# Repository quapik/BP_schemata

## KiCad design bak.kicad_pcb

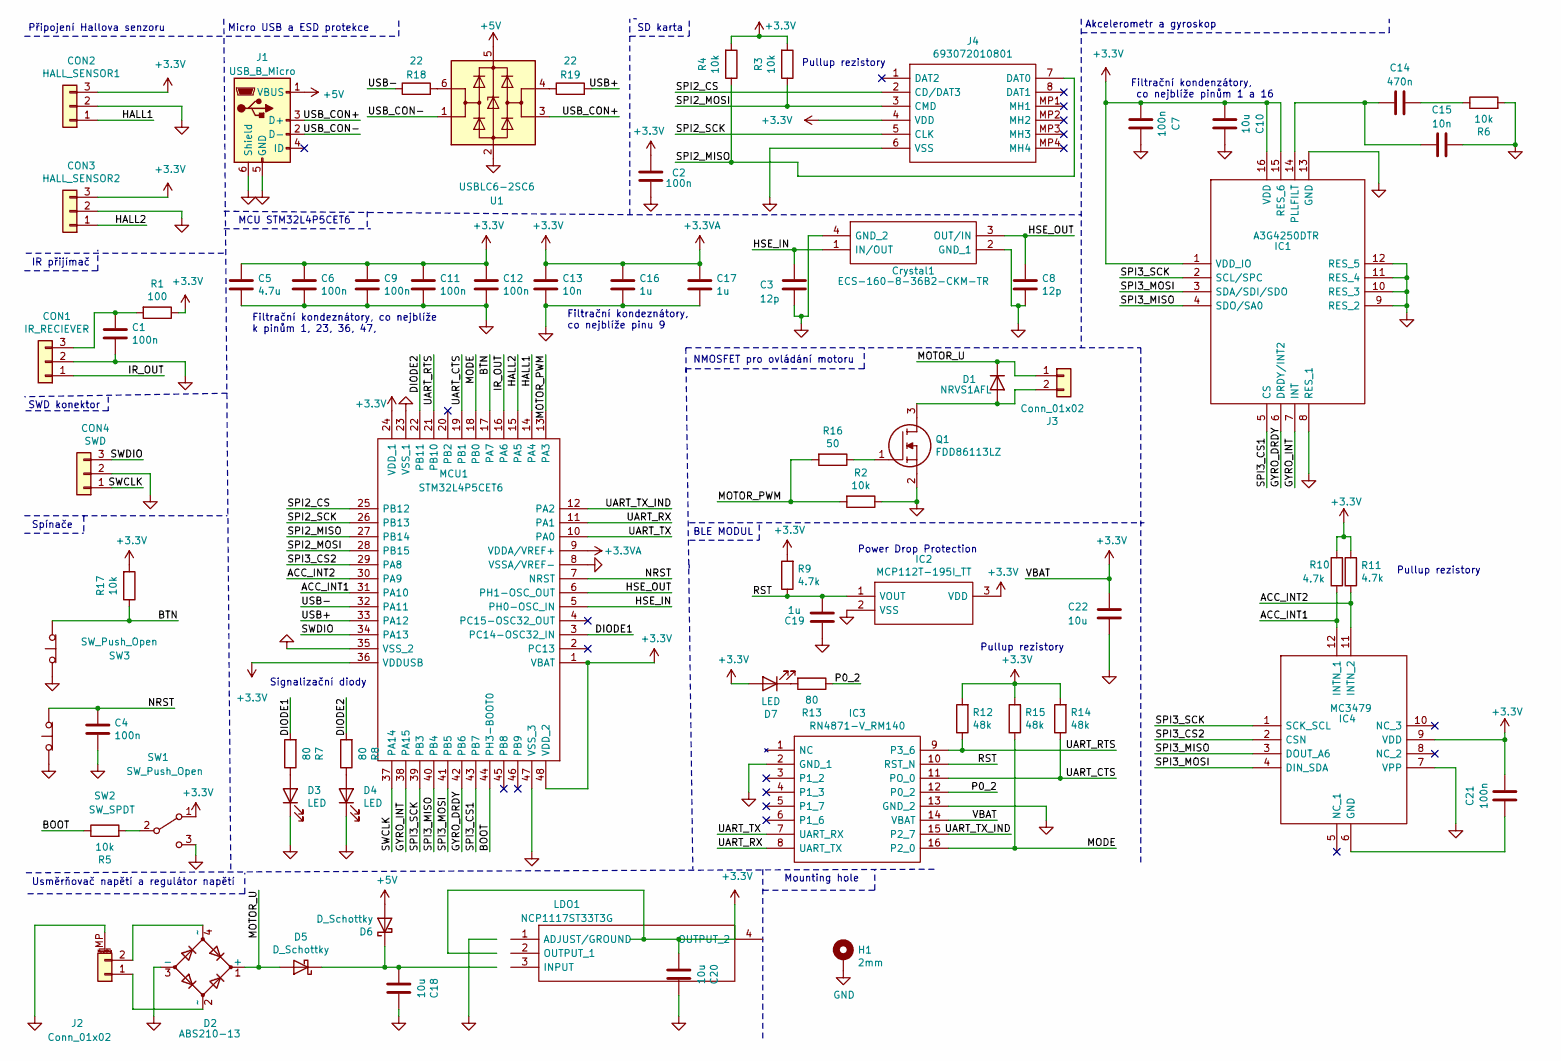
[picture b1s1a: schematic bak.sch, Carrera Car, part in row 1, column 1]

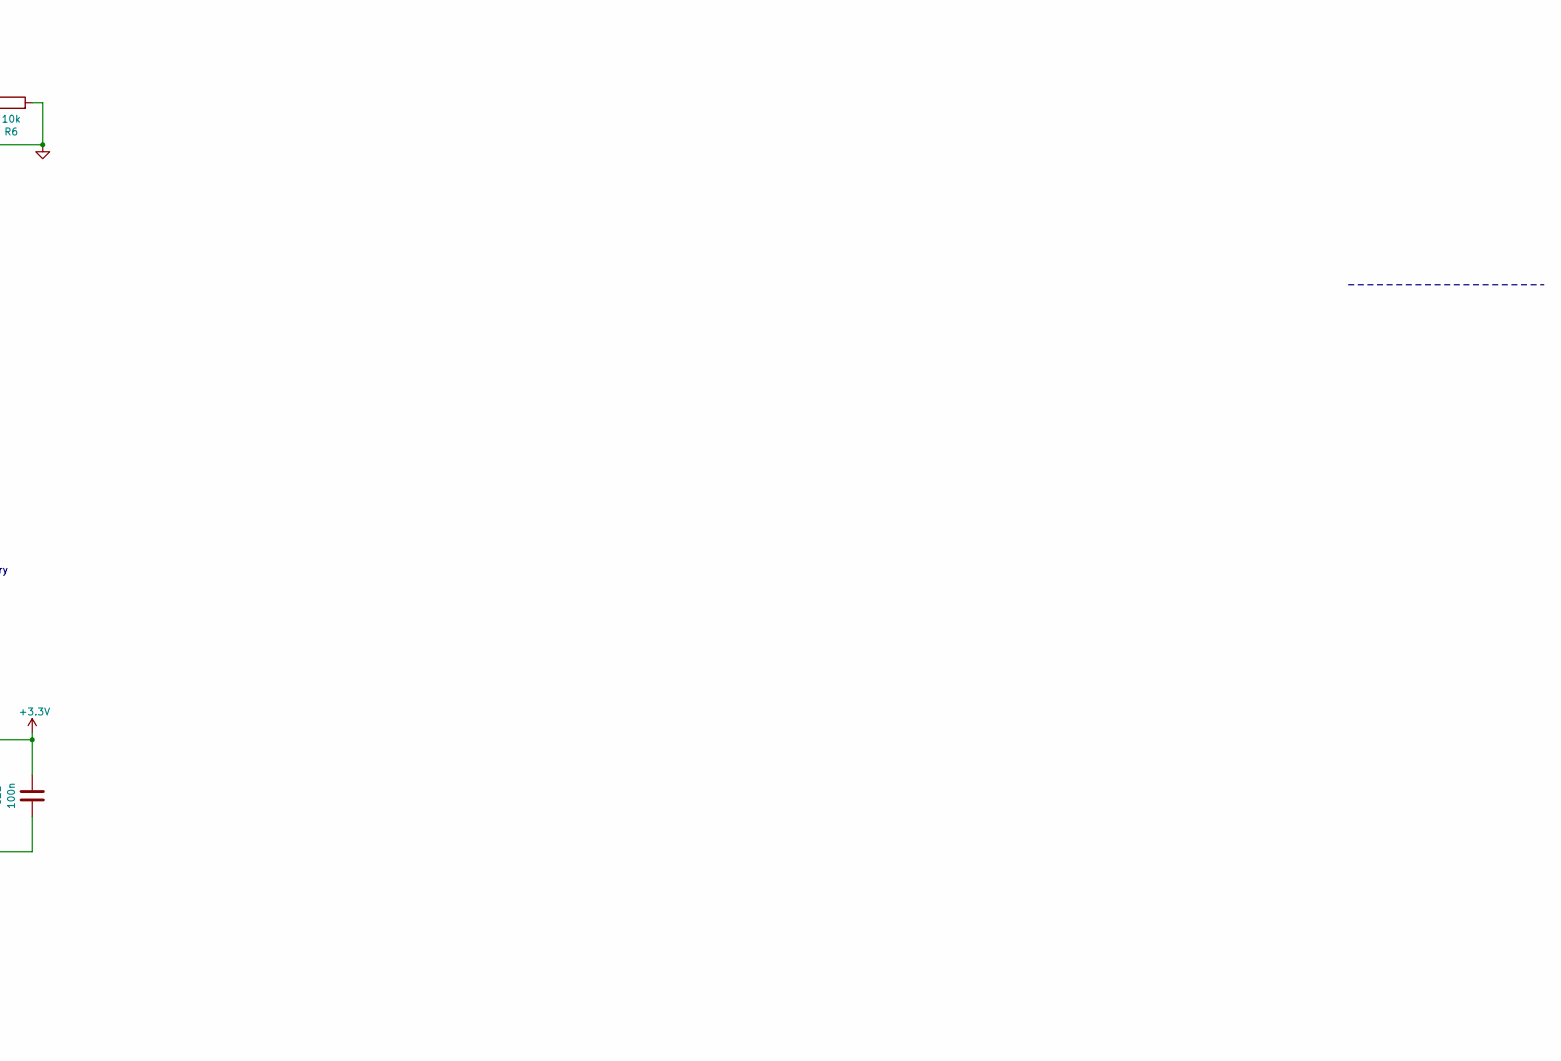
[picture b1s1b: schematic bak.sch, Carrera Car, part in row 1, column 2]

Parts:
C1, C2, C4, C6, C7, C9, C11, C12, C21: 100n; C_0805_2012Metric_Pad1.18x1.45mm_HandSolder
C3, C8: 12p; C_0603_1608Metric_Pad1.08x0.95mm_HandSolder
C5: 4.7u; C_0603_1608Metric_Pad1.08x0.95mm_HandSolder
C10, C22: 10u; C_0805_2012Metric_Pad1.18x1.45mm_HandSolder
C13, C15: 10n; C_0603_1608Metric_Pad1.08x0.95mm_HandSolder
C14: 470n; C_0603_1608Metric_Pad1.08x0.95mm_HandSolder
C16, C17, C19: 1u; C_0603_1608Metric_Pad1.08x0.95mm_HandSolder
C18, C20: 10u; C_1210_3225Metric_Pad1.33x2.70mm_HandSolder
CON1: IR_RECIEVER; MyConnector3
CON2: HALL_SENSOR1; MyConnector3
CON3: HALL_SENSOR2; MyConnector3
CON4: SWD; MyConnector3
Crystal1: ECS-160-8-36B2-CKM-TR; ECS160836B2CKMTR; Mouser Part Number 520-160-8-36B2-CKMTR
D1: NRVS1AFL; D_SOD-123F
D2: ABS210-13; ABS21013
D3, D4, D7: LED; D_0805_2012Metric_Pad1.15x1.40mm_HandSolder
D5, D6: D_Schottky; D_SOD-323_HandSoldering
H1: 2mm; MountingHole_2.7mm_M2.5_Pad_Via
IC1: A3G4250DTR; LGA-16L_4X4X1.1MM_; Mouser Part Number 511-A3G4250DTR
IC2: MCP112T-195I_TT; SOT95P237X112-3N; Mouser Part Number 579-MCP112T-195I/TT
IC3: RN4871-V_RM140; RN4871VRM140; Mouser Part Number 579-RN4871-V/RM140
IC4: MC3479; Mouser Part Number 498-MC3479
J1: USB_B_Micro; USB30653000A
J2: Conn_01x02; Conn01x02_my
J3: Conn_01x02; MyConnector2
J4: 693072010801; Mouser Part Number 710-693072010801
LDO1: NCP1117ST33T3G; SOT230P700X180-4N; Mouser Part Number 863-NCP1117ST33T3G
MCU1: STM32L4P5CET6; QFP50P900X900X160-48N; Mouser Part Number 511-STM32L4P5CET6
Q1: FDD86113LZ; DPAK3-CASE-369AS; Mouser Part Number 512-FDD86113LZ
R1: 100; R_0805_2012Metric_Pad1.20x1.40mm_HandSolder
R2, R3, R4, R5, R6, R17: 10k; R_0805_2012Metric_Pad1.20x1.40mm_HandSolder
R7, R8, R13: 80; R_0805_2012Metric_Pad1.20x1.40mm_HandSolder
R9, R10, R11: 4.7k; R_0603_1608Metric_Pad0.98x0.95mm_HandSolder
R12, R14, R15: 48k; R_0603_1608Metric_Pad0.98x0.95mm_HandSolder
R16: 50; R_0805_2012Metric_Pad1.20x1.40mm_HandSolder
R18, R19: 22; R_0603_1608Metric_Pad0.98x0.95mm_HandSolder
SW1, SW3: SW_Push_Open; PTS815SJM250SMTRLFS
SW2: SW_SPDT; SSSS810701
U1: USBLC6-2SC6; SOT-23-6

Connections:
+3.3VA: C2.2, C5.1, C6.1, C7.2, C9.1, C10.2, C11.1, C12.1, C13.1, C16.1, C17.1, C20.2, C21.2, C22.1, CON2.3, CON3.3, D7.2 (A), IC1.1 (VDD_IO), IC1.15 (RES_6), IC1.16 (VDD), IC2.3 (VDD), IC3.14 (VBAT), IC4.9 (VDD), J4.4 (VDD), LDO1.2 (OUTPUT_1), LDO1.4 (OUTPUT_2), MCU1.1 (VBAT), MCU1.9 (VDDA/VREF+), MCU1.24 (VDD_1), MCU1.36 (VDDUSB), MCU1.48 (VDD_2), R1.1, R3.2, R4.2, R9.2, R10.2, R11.2, R12.2, R14.2, R15.2, R17.2, SW2.1 (A)
+5V: D6.2 (A), J1.1 (VBUS), U1.5 (VBUS)
/ACC_INT1: IC4.12 (INTN_1), MCU1.31 (PA10), R10.1
/ACC_INT2: IC4.11 (INTN_2), MCU1.30 (PA9), R11.1
/BOOT: MCU1.44 (PH3-BOOT0), R5.1
/BTN: MCU1.17 (PA7), R17.1, SW3.2 (B)
/DIODE1: MCU1.3 (PC14-OSC32_IN), R7.2
/DIODE2: MCU1.22 (PB11), R8.2
/GYRO_DRDY: IC1.6 (DRDY/INT2), MCU1.42 (PB6)
/GYRO_INT: IC1.7 (INT), MCU1.38 (PA15)
/HALL1: CON2.1, MCU1.14 (PA4)
/HALL2: CON3.1, MCU1.15 (PA5)
/HSE_IN: C3.1, Crystal1.1 (IN/OUT), MCU1.5 (PH0-OSC_IN)
/HSE_OUT: C8.1, Crystal1.3 (OUT/IN), MCU1.6 (PH1-OSC_OUT)
/IR_OUT: CON1.1, MCU1.16 (PA6)
/MODE: IC3.16 (P2_0), MCU1.18 (PB0), R15.1
/MOTOR+: D1.1 (K), D2.1 (+), D5.2 (A), J3.1
/MOTOR-: D1.2 (A), J3.2, Q1.3
/MOTOR_PWM: MCU1.13 (PA3), R2.2, R16.2
/NRST: C4.1, MCU1.7 (NRST), SW1.2 (B)
/P0_2: IC3.12 (P0_2), R13.1
/RST: C19.1, IC2.1 (VOUT), IC3.10 (RST_N), R9.1
/SPI2_CS: J4.2 (CD/DAT3), MCU1.25 (PB12)
/SPI2_MISO: J4.7 (DAT0), MCU1.27 (PB14), R4.1
/SPI2_MOSI: J4.3 (CMD), MCU1.28 (PB15), R3.1
/SPI2_SCK: J4.5 (CLK), MCU1.26 (PB13)
/SPI3_CS1: IC1.5 (CS), MCU1.43 (PB7)
/SPI3_CS2: IC4.2 (CSN), MCU1.29 (PA8)
/SPI3_MISO: IC1.4 (SDO/SA0), IC4.3 (DOUT_A6), MCU1.40 (PB4)
/SPI3_MOSI: IC1.3 (SDA/SDI/SDO), IC4.4 (DIN_SDA), MCU1.41 (PB5)
/SPI3_SCK: IC1.2 (SCL/SPC), IC4.1 (SCK_SCL), MCU1.39 (PB3)
/SWCLK: CON4.1, MCU1.37 (PA14)
/SWDIO: CON4.3, MCU1.34 (PA13)
/UART_CTS: IC3.11 (PO_0), MCU1.19 (PB1), R14.1
/UART_RTS: IC3.9 (P3_6), MCU1.21 (PB10), R12.1
/UART_RX: IC3.8 (UART_TX), MCU1.11 (PA1)
/UART_TX: IC3.7 (UART_RX), MCU1.10 (PA0)
/UART_TX_IND: IC3.15 (P2_7), MCU1.12 (PA2)
/USB+: MCU1.33 (PA12), R19.2
/USB-: MCU1.32 (PA11), R18.1
/USB_CON+: J1.3 (D+), U1.3 (I/O2)
/USB_CON-: J1.2 (D-), U1.1 (I/O1)
GND: C1.1, C2.1, C3.2, C4.2, C5.2, C6.2, C7.1, C8.2, C9.2, C10.1, C11.2, C12.2, C13.2, C15.1, C16.2, C17.2, C18.1, C19.2, C20.1, C22.2, CON1.2, CON2.2, CON3.2, CON4.2, Crystal1.2 (GND_1), Crystal1.4 (GND_2), D2.3 (-), D3.1 (K), D4.1 (K), H1.1, IC1.8 (RES_1), IC1.9 (RES_2), IC1.10 (RES_3), IC1.11 (RES_4), IC1.12 (RES_5), IC1.13 (GND), IC2.2 (VSS), IC3.2 (GND_1), IC3.13 (GND_2), IC4.7 (VPP), J1.5 (GND), J1.6 (Shield), J2.MP (MountPin), J4.6 (VSS), LDO1.1 (ADJUST/GROUND), MCU1.8 (VSSA/VREF-), MCU1.23 (VSS_1), MCU1.35 (VSS_2), MCU1.47 (VSS_3), Q1.2, R2.1, R6.2, SW1.1 (A), SW2.3 (C), SW3.1 (A), U1.2 (GND)
unnamed: C1.2, CON1.3, R1.2
unnamed: C14.1, R6.1
unnamed: C14.2, C15.2, IC1.14 (PLLFILT)
unnamed: C21.1, IC4.6 (GND)
unnamed: D2.2 (~~), J2.1
unnamed: D2.4 (~~), J2.2
unnamed: D3.2 (A), R7.1
unnamed: D4.2 (A), R8.1
unnamed: D7.1 (K), R13.2
unnamed: Q1.1, R16.1
unnamed: R5.2, SW2.2 (B)
unnamed: R18.2, U1.6 (I/O1)
unnamed: R19.1, U1.4 (I/O2)

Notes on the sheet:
Micro USB a ESD protekce
MCU STM32L4P5CET6
Usměrňovač napětí a regulátor napětí
SD karta
NMOSFET pro ovládání motoru
BLE MODUL
Spínače
Mounting hole
Připojení Hallova senzoru
Filtrační kondenzátory, co nejblíže pinům 1 a 16
Akcelerometr a gyroskop
Signalizační diody
Pullup rezistory
Power Drop Protection
Filtrační kondeznátory, co nejblíže k pinům 1, 23, 36, 47,
Filtrační kondeznátory, co nejblíže pinu 9
Pullup rezistory
IR přijímač
SWD konektor

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
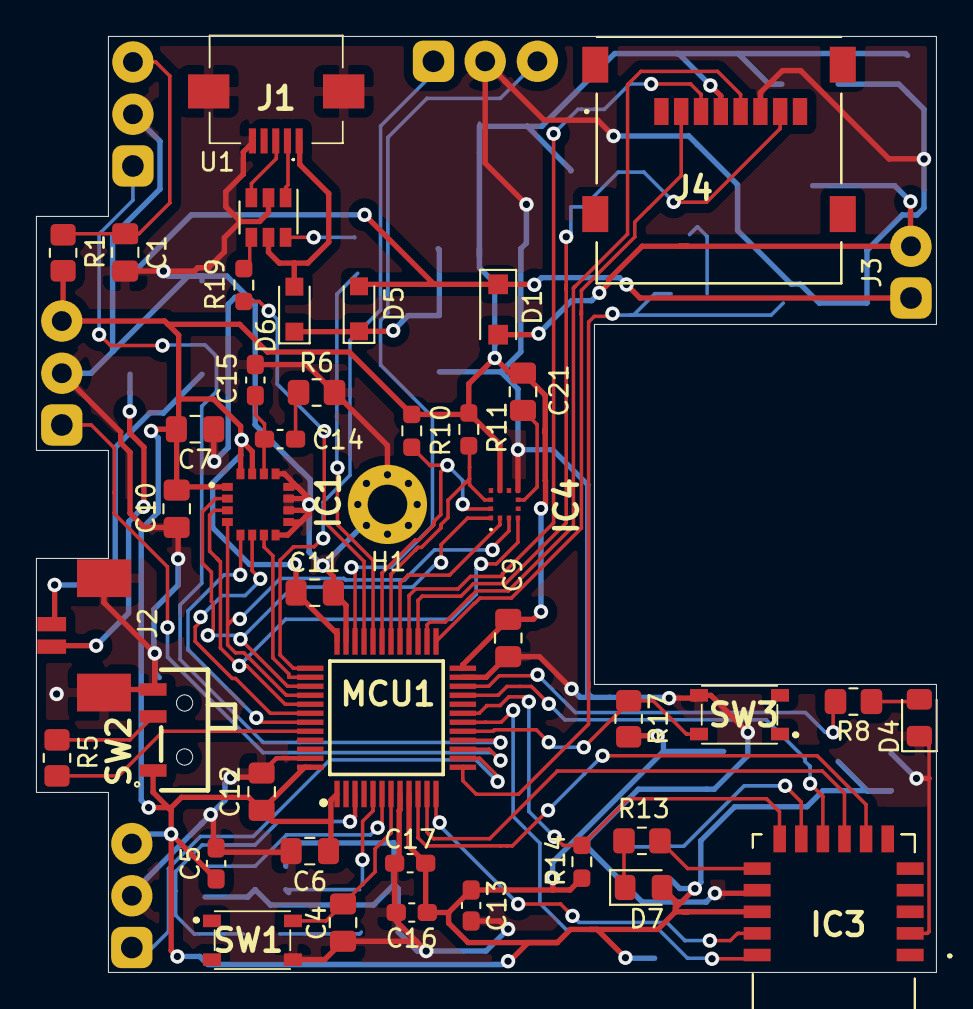
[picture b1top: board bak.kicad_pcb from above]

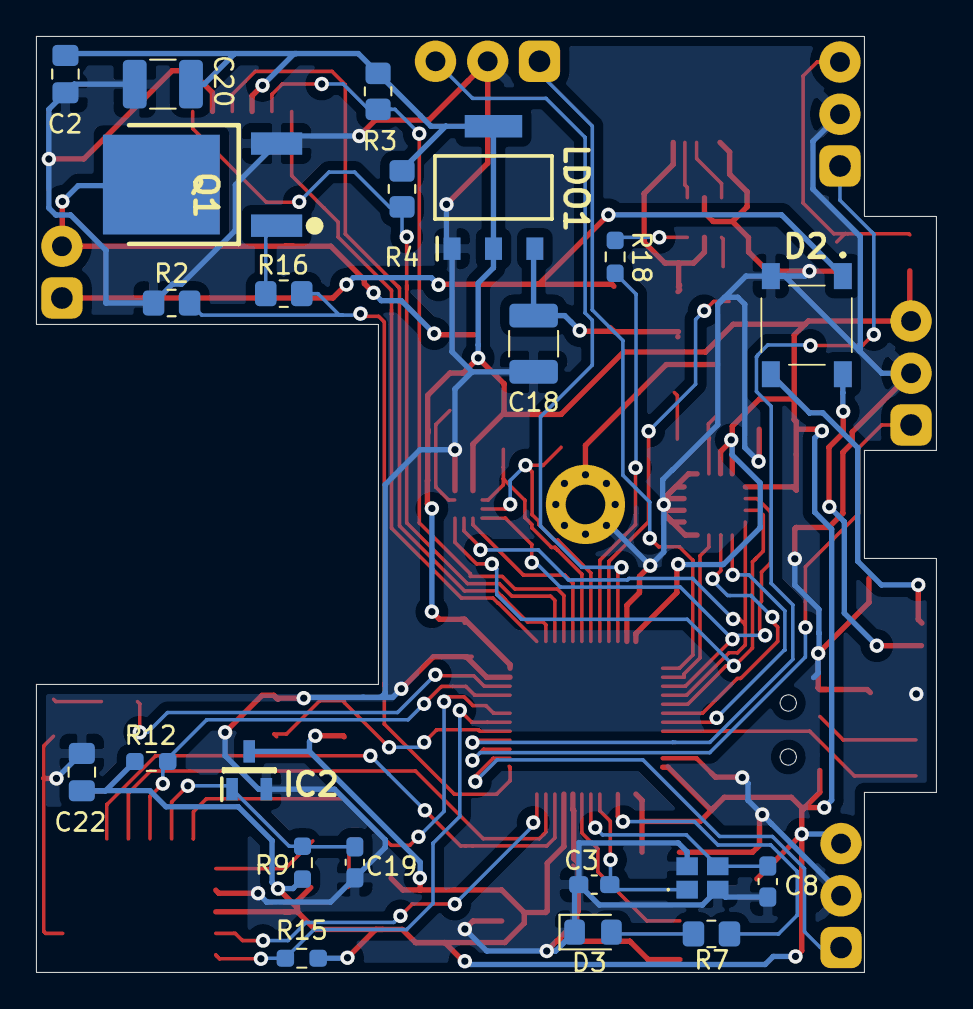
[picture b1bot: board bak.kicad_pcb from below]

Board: 2 copper layers, 50.0 x 52.0 mm, 69 parts (22 on the bottom side), 57 nets.

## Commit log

2022-05-05 first version upload
2022-05-05 update test
2022-05-05 update sch test2
2022-05-05 update predelane piny a spi
2022-05-06 pred ble modulem uprava
2022-05-06 cca predelano
2022-05-07 hotovo_snad
2022-05-07 snad final, zony, upraveny 3D modely, upraveny tlacitko
2022-05-09 final_version2_snad
2022-05-09 FINAL VER2
2022-07-15 final
